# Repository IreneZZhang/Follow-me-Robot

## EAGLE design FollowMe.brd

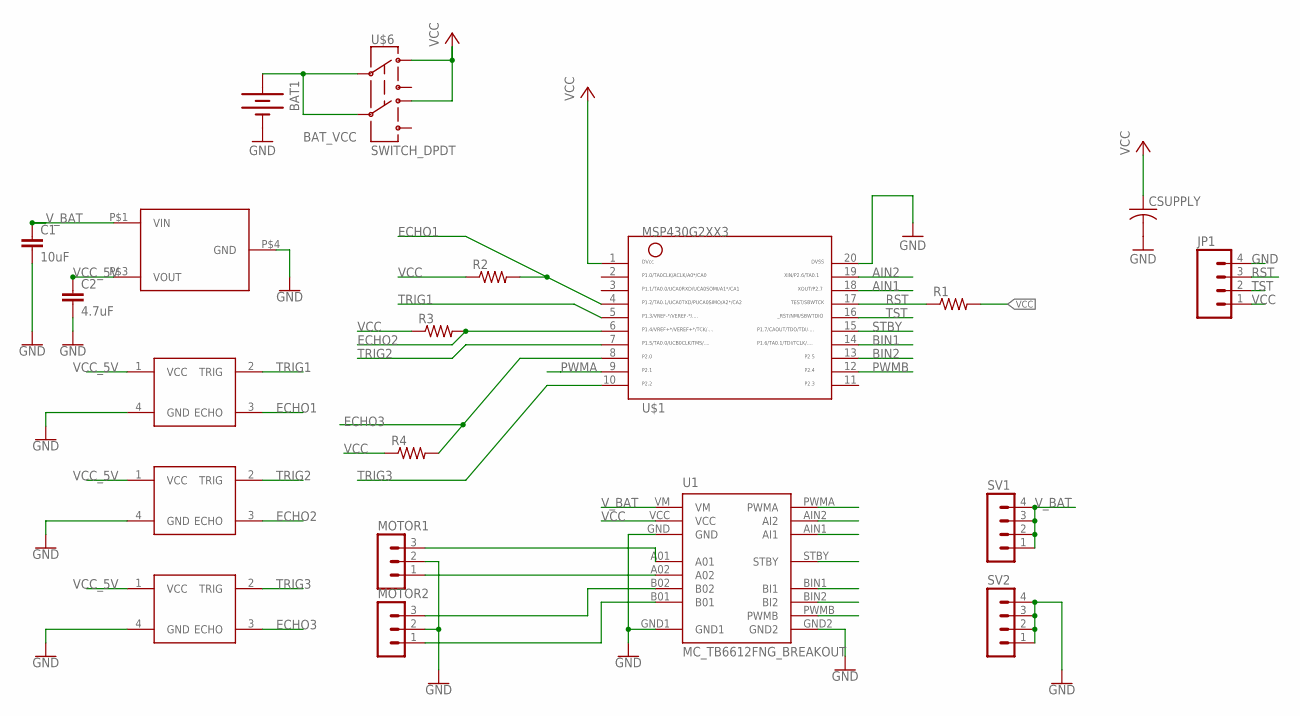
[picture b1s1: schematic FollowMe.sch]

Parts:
BAT1: BATTERY; BATTERY_PACK_2AA
C1: 10uF; 1206
C2: 4.7uF; 1206
CSUPPLY: C-USC1206; C1206
JP1: M04LOCK; 1X04_LOCK
MOTOR1, MOTOR2: MA03-1
R1, R2, R3, R4: R-US_R1206; R1206
SV1, SV2: MA04-1
U1: MC_TB6612FNG_BREAKOUT; MC_TB6612FNG
U$1: MSP430G2XX3TSSOP; PW20
U$2: LDO
U$3, U$4, U$5: ULTRASONIC
U$6: SWITCH_DPDT; JS_DPDT_TH

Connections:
AIN1: U1.AIN1 (AI1), U$1.18
AIN2: U1.AIN2 (AI2), U$1.19
BAT_VCC: BAT1.3V (+), U$6.2, U$6.5
BIN1: U1.BIN1 (BI1), U$1.14
BIN2: U1.BIN2 (BI2), U$1.13
ECHO1: R2.2, U$1.4, U$3.3 (ECHO)
ECHO2: R3.2, U$1.6, U$4.3 (ECHO)
ECHO3: R4.2, U$1.8, U$5.3 (ECHO)
GND: BAT1.GND (-), C1.2, C2.2, CSUPPLY.2, JP1.4, MOTOR1.2, MOTOR2.2, SV2.1, SV2.2, SV2.3, SV2.4, U1.GND, U1.GND1, U1.GND2, U$1.20, U$2.P$4 (GND), U$3.4 (GND), U$4.4 (GND), U$5.4 (GND)
unnamed: MOTOR1.3, U1.A01
unnamed: MOTOR1.1, U1.A02
unnamed: MOTOR2.3, U1.B02
unnamed: MOTOR2.1, U1.B01
PWMA: U1.PWMA, U$1.9
PWMB: U1.PWMB, U$1.12
RST: JP1.3, R1.1, U$1.17
STBY: U1.STBY, U$1.15
TRIG1: U$1.5, U$3.2 (TRIG)
TRIG2: U$1.7, U$4.2 (TRIG)
TRIG3: U$1.10, U$5.2 (TRIG)
TST: JP1.2, U$1.16
VCC: CSUPPLY.1, JP1.1, R1.2, R2.1, R3.1, R4.1, U1.VCC, U$1.1, U$6.1, U$6.4
VCC_5V: C2.1, U$2.P$3 (VOUT), U$3.1 (VCC), U$4.1 (VCC), U$5.1 (VCC)
V_BAT: C1.1, SV1.1, SV1.2, SV1.3, SV1.4, U1.VM, U$2.P$1 (VIN)

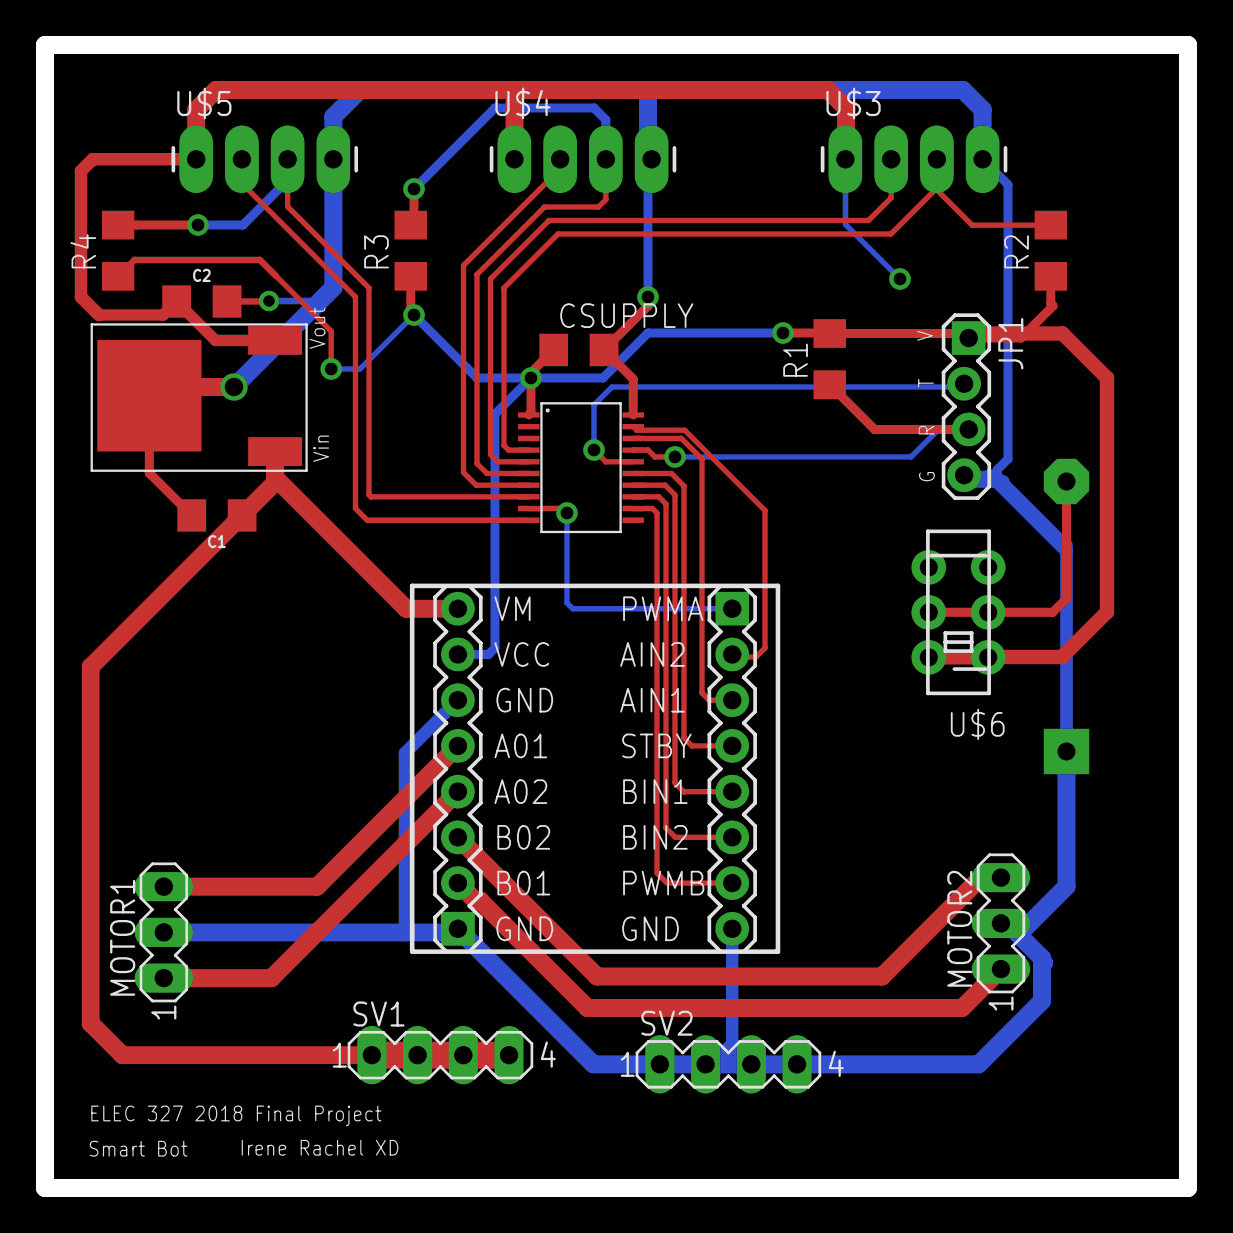
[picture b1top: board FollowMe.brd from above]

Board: 2 copper layers, 63.5 x 63.5 mm, 20 parts (1 on the bottom side), 24 nets.

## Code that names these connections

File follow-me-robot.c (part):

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#include <msp430.h>

/* Motor Pins*/
#define PWMA BIT1
#define PWMB BIT4
#define AIN1 BIT7
#define AIN2 BIT6
#define BIN1 BIT6
#define BIN2 BIT5
#define STBY BIT7

/* Sensor Pins */
#define TRIG1 BIT3
#define ECHO1 BIT2
#define TRIG2 BIT5
#define ECHO2 BIT4
#define TRIG3 BIT2
#define ECHO3 BIT0


/* Function Prototypes */
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    // Motor Pins
    P1DIR |= STBY + BIN1;
    P2DIR |= PWMA + PWMB + AIN1 + AIN2 + BIN2;
    P1SEL &= ~(STBY + BIN1 + BIT1);    // use pins as GPIO
    P2SEL &= ~(BIN2 + AIN1 + AIN2);

    // Set up PWMs
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
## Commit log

2018-05-03 final project

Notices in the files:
parts and their libraries:
SparkFun: Licensing: CC v3.0 Share-Alike You are welcome to use this library for commercial purposes.
SparkFun-Capacitors: Licensing: Creative Commons ShareAlike 4.0 International - https://creativecommons.org/licenses/by-sa/4.0
